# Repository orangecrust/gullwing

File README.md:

# Gullwing Keyboard
Basic layout based on the [re-gret](https://github.com/rschenk/re-gret).

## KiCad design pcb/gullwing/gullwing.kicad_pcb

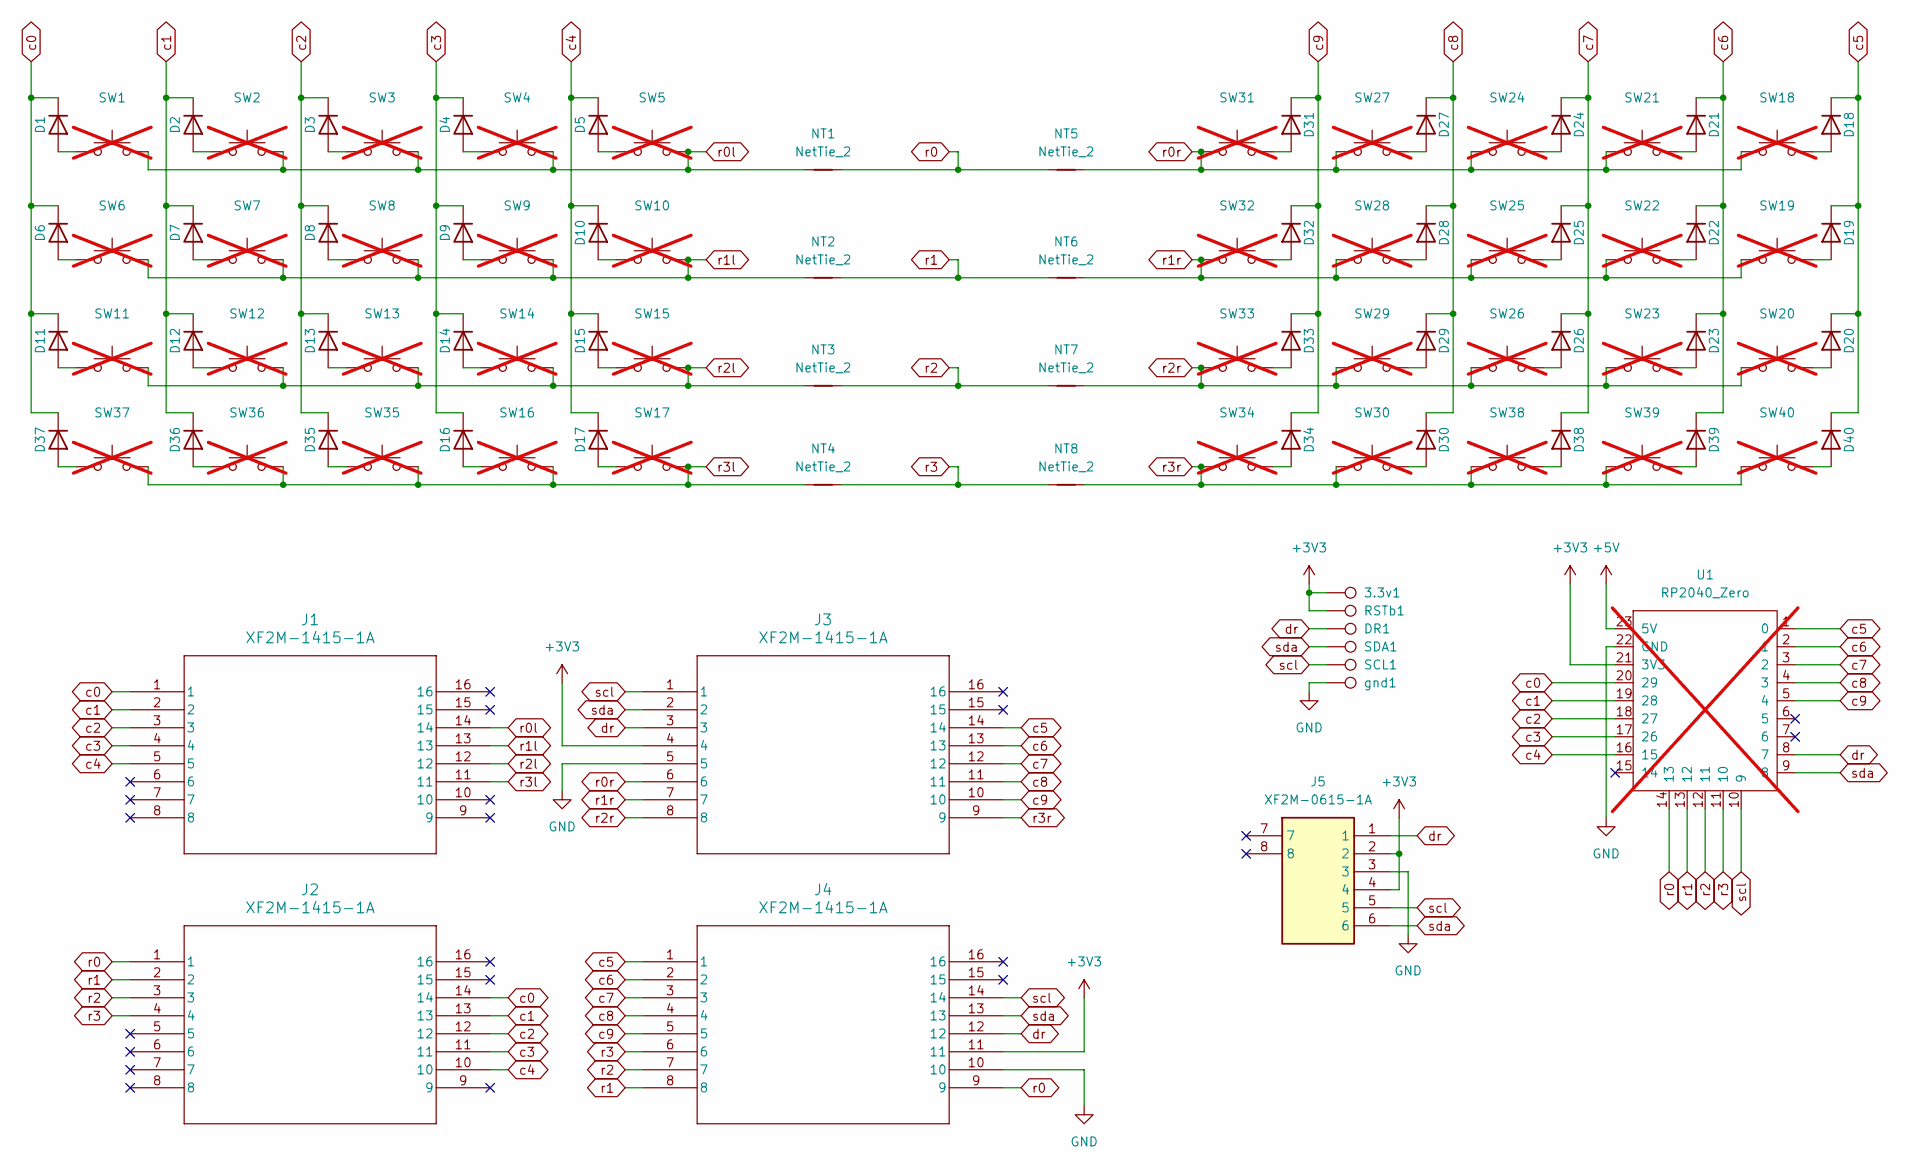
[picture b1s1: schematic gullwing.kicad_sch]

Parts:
3.3v1: TestPoint; TestPoint_Pad_1.0x1.0mm
D1, D2, D3, D4, D5, D6, D7, D8, D9, D10, D11, D12, D13, D14, D15, D16, D17, D18, D19, D20, D21, D22, D23, D24, D25, D26, D27, D28, D29, D30, D31, D32, D33, D34, D35, D36, D37, D38, D39, D40: Diode_SOD-123
DR1: TestPoint; TestPoint_Pad_1.0x1.0mm
J1, J2, J3, J4: XF2M-1415-1A; CON14_1X14_DRB_XF2C_TYC
J5: XF2M-0615-1A; XF2M06151A; Mouser Part Number 653-XF2M-0615-1A
NT1, NT2, NT3, NT4, NT5, NT6, NT7, NT8: NetTie_2; NetTie-2_SMD_Pad0.5mm
RSTb1: TestPoint; TestPoint_Pad_1.0x1.0mm
SCL1: TestPoint; TestPoint_Pad_1.0x1.0mm
SDA1: TestPoint; TestPoint_Pad_1.0x1.0mm
SW1, SW2, SW3, SW4, SW5, SW6, SW7, SW8, SW9, SW10, SW11, SW12, SW13, SW14, SW15, SW16, SW17, SW18, SW19, SW20, SW21, SW22, SW23, SW24, SW25, SW26, SW27, SW28, SW29, SW30, SW31, SW32, SW33, SW34, SW35, SW36, SW37, SW38, SW39, SW40: Hotswap_Choc_V1V2_1.00u; not fitted
U1: RP2040_Zero; not fitted
gnd1: TestPoint; TestPoint_Pad_1.0x1.0mm

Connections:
+3V3: 3.3v1.1, J3.4, J4.11, J5.2, J5.4, RSTb1.1, U1.21 (3V3)
+5V: U1.23 (5V)
GND: J3.5, J4.10, J5.3, U1.22 (GND), gnd1.1
unnamed: D1.2 (A), SW1.1
unnamed: D2.2 (A), SW2.1
unnamed: D3.2 (A), SW3.1
unnamed: D4.2 (A), SW4.1
unnamed: D5.2 (A), SW5.1
unnamed: D6.2 (A), SW6.1
unnamed: D7.2 (A), SW7.1
unnamed: D8.2 (A), SW8.1
unnamed: D9.2 (A), SW9.1
unnamed: D10.2 (A), SW10.1
unnamed: D11.2 (A), SW11.1
unnamed: D12.2 (A), SW12.1
unnamed: D13.2 (A), SW13.1
unnamed: D14.2 (A), SW14.1
unnamed: D15.2 (A), SW15.1
unnamed: D16.2 (A), SW16.1
unnamed: D17.2 (A), SW17.1
unnamed: D18.2 (A), SW18.1
unnamed: D19.2 (A), SW19.1
unnamed: D20.2 (A), SW20.1
unnamed: D21.2 (A), SW21.1
unnamed: D22.2 (A), SW22.1
unnamed: D23.2 (A), SW23.1
unnamed: D24.2 (A), SW24.1
unnamed: D25.2 (A), SW25.1
unnamed: D26.2 (A), SW26.1
unnamed: D27.2 (A), SW27.1
unnamed: D28.2 (A), SW28.1
unnamed: D29.2 (A), SW29.1
unnamed: D30.2 (A), SW30.1
unnamed: D31.2 (A), SW31.1
unnamed: D32.2 (A), SW32.1
unnamed: D33.2 (A), SW33.1
unnamed: D34.2 (A), SW34.1
unnamed: D35.2 (A), SW35.1
unnamed: D36.2 (A), SW36.1
unnamed: D37.2 (A), SW37.1
unnamed: D38.2 (A), SW38.1
unnamed: D39.2 (A), SW39.1
unnamed: D40.2 (A), SW40.1
c0: D1.1 (K), D6.1 (K), D11.1 (K), D37.1 (K), J1.1, J2.14, U1.20 (29)
c1: D2.1 (K), D7.1 (K), D12.1 (K), D36.1 (K), J1.2, J2.13, U1.19 (28)
c2: D3.1 (K), D8.1 (K), D13.1 (K), D35.1 (K), J1.3, J2.12, U1.18 (27)
c3: D4.1 (K), D9.1 (K), D14.1 (K), D16.1 (K), J1.4, J2.11, U1.17 (26)
c4: D5.1 (K), D10.1 (K), D15.1 (K), D17.1 (K), J1.5, J2.10, U1.16 (15)
c5: D18.1 (K), D19.1 (K), D20.1 (K), D40.1 (K), J3.14, J4.1, U1.1 (0)
c6: D21.1 (K), D22.1 (K), D23.1 (K), D39.1 (K), J3.13, J4.2, U1.2 (1)
c7: D24.1 (K), D25.1 (K), D26.1 (K), D38.1 (K), J3.12, J4.3, U1.3 (2)
c8: D27.1 (K), D28.1 (K), D29.1 (K), D30.1 (K), J3.11, J4.4, U1.4 (3)
c9: D31.1 (K), D32.1 (K), D33.1 (K), D34.1 (K), J3.10, J4.5, U1.5 (4)
dr: DR1.1, J3.3, J4.12, J5.1, U1.8 (7)
r0: J2.1, J4.9, NT1.2, NT5.1, U1.14 (13)
r0l: J1.14, NT1.1, SW1.2, SW2.2, SW3.2, SW4.2, SW5.2
r0r: J3.6, NT5.2, SW18.2, SW21.2, SW24.2, SW27.2, SW31.2
r1: J2.2, J4.8, NT2.2, NT6.1, U1.13 (12)
r1l: J1.13, NT2.1, SW6.2, SW7.2, SW8.2, SW9.2, SW10.2
r1r: J3.7, NT6.2, SW19.2, SW22.2, SW25.2, SW28.2, SW32.2
r2: J2.3, J4.7, NT3.2, NT7.1, U1.12 (11)
r2l: J1.12, NT3.1, SW11.2, SW12.2, SW13.2, SW14.2, SW15.2
r2r: J3.8, NT7.2, SW20.2, SW23.2, SW26.2, SW29.2, SW33.2
r3: J2.4, J4.6, NT4.2, NT8.1, U1.11 (10)
r3l: J1.11, NT4.1, SW16.2, SW17.2, SW35.2, SW36.2, SW37.2
r3r: J3.9, NT8.2, SW30.2, SW34.2, SW38.2, SW39.2, SW40.2
scl: J3.1, J4.14, J5.5, SCL1.1, U1.10 (9)
sda: J3.2, J4.13, J5.6, SDA1.1, U1.9 (8)

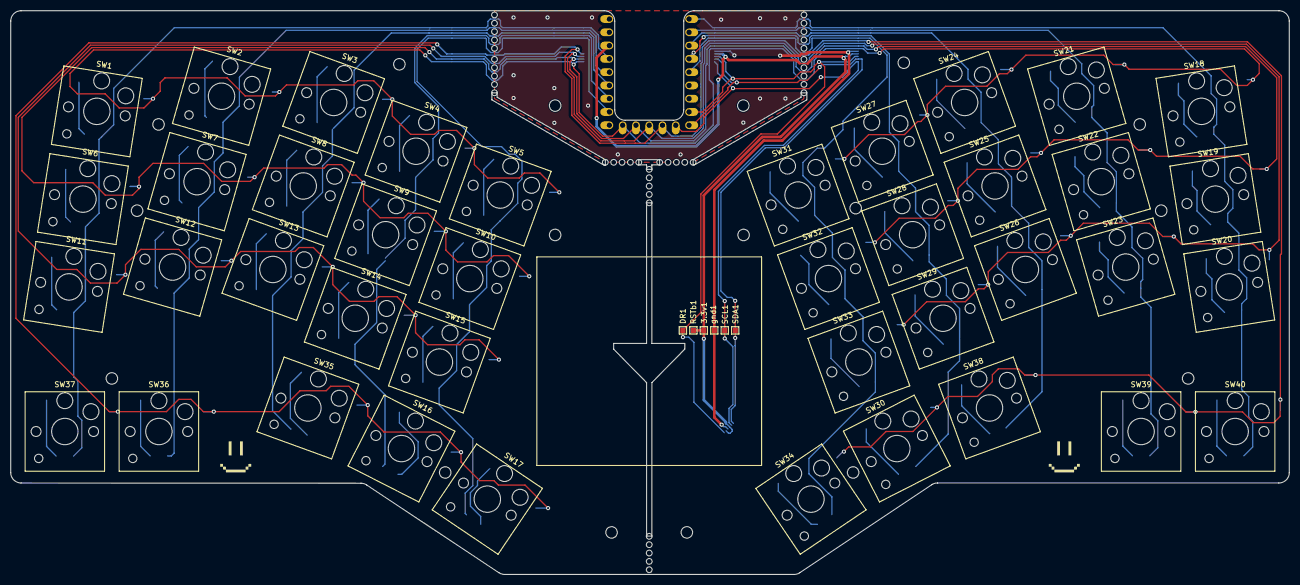
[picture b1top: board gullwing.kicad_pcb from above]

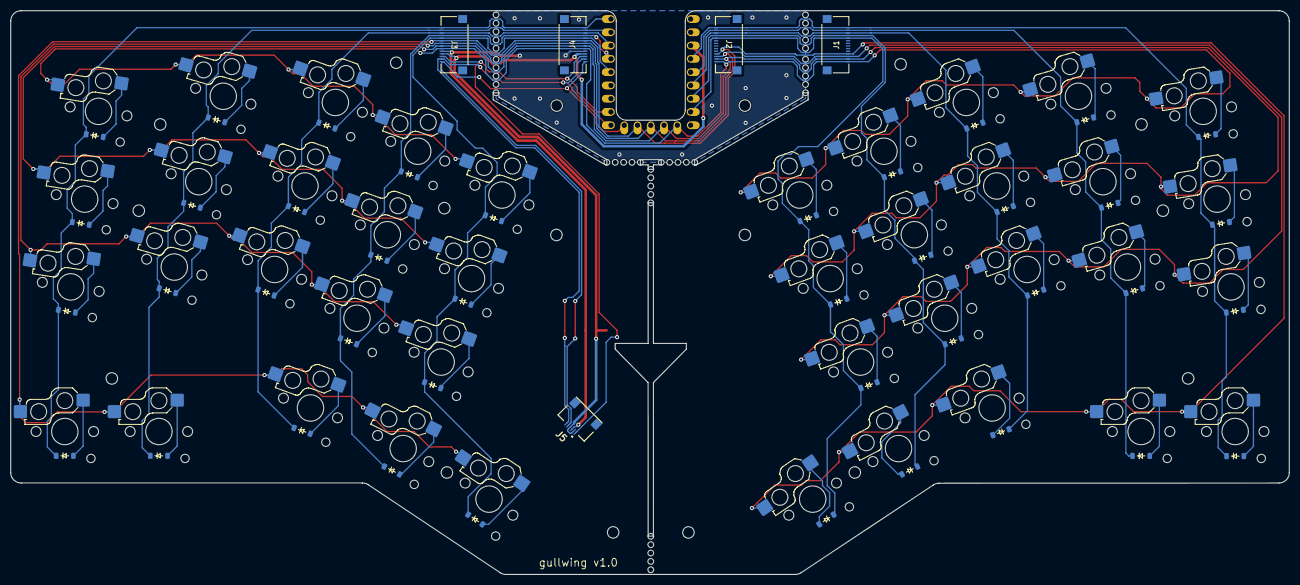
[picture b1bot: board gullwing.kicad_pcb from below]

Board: 2 copper layers, 244.6 x 107.8 mm, 125 parts (53 on the bottom side), 67 nets.

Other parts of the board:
PAD5, PAD6, PAD7, PAD8, PAD8#2, PAD8#3, PAD8#4, PAD8#5, PAD8#6, PAD8#7, PAD8#8, PAD8#9, PAD8#10, PAD8#11, PAD10, PAD11, PAD12: MountingHole_2.2mm_M2
mb1, mb2, mb2#2, mb2#3, mb2#4, mb2#5, mb3, mb4: Mouse_Bites_5

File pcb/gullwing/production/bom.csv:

Designator,Footprint,Quantity,Value,LCSC Part #
"3.3V1, DR1, GND1, RSTB1, SCL1, SDA1",TestPoint_Pad_1.0x1.0mm,6,TestPoint,
"D1, D10, D11, D12, D13, D14, D15, D16, D17, D18, D19, D2, D20, D21, D22, D23, D24, D25, D26, D27, D28, D29, D3, D30, D31, D32, D33, D34, D35, D36, D37, D38, D39, D4, D40, D5, D6, D7, D8, D9",Diode_SOD-123,40,~,C7462829
"J1, J2, J3, J4",CON14_1X14_DRB_XF2C_TYC,4,XF2M-1415-1A,C397114
J5,XF2M06151A,1,XF2M-0615-1A,C308993
"MB1, MB2_5, MB2_4, MB2_3, MB2_2, MB2, MB3, MB4",Mouse_Bites_5,8,Mouse_Bites_5,

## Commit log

2025-08-16 basic routing done
    todo:
    touchpad i2c/dr conneciton & routing
    expand horizontally
2025-08-17 done -- first pass
2025-08-21 done -- ready for export
2025-08-21 adding production files
2025-08-21 updating name
2025-09-15 adding zmk firmware
2025-09-15 moving github workflow location
2025-09-15 updating build.yaml
2025-09-15 moving build.yaml
